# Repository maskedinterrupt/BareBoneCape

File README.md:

# BareBone Cape
### A BeagleBone Black Cape Template made in KiCad

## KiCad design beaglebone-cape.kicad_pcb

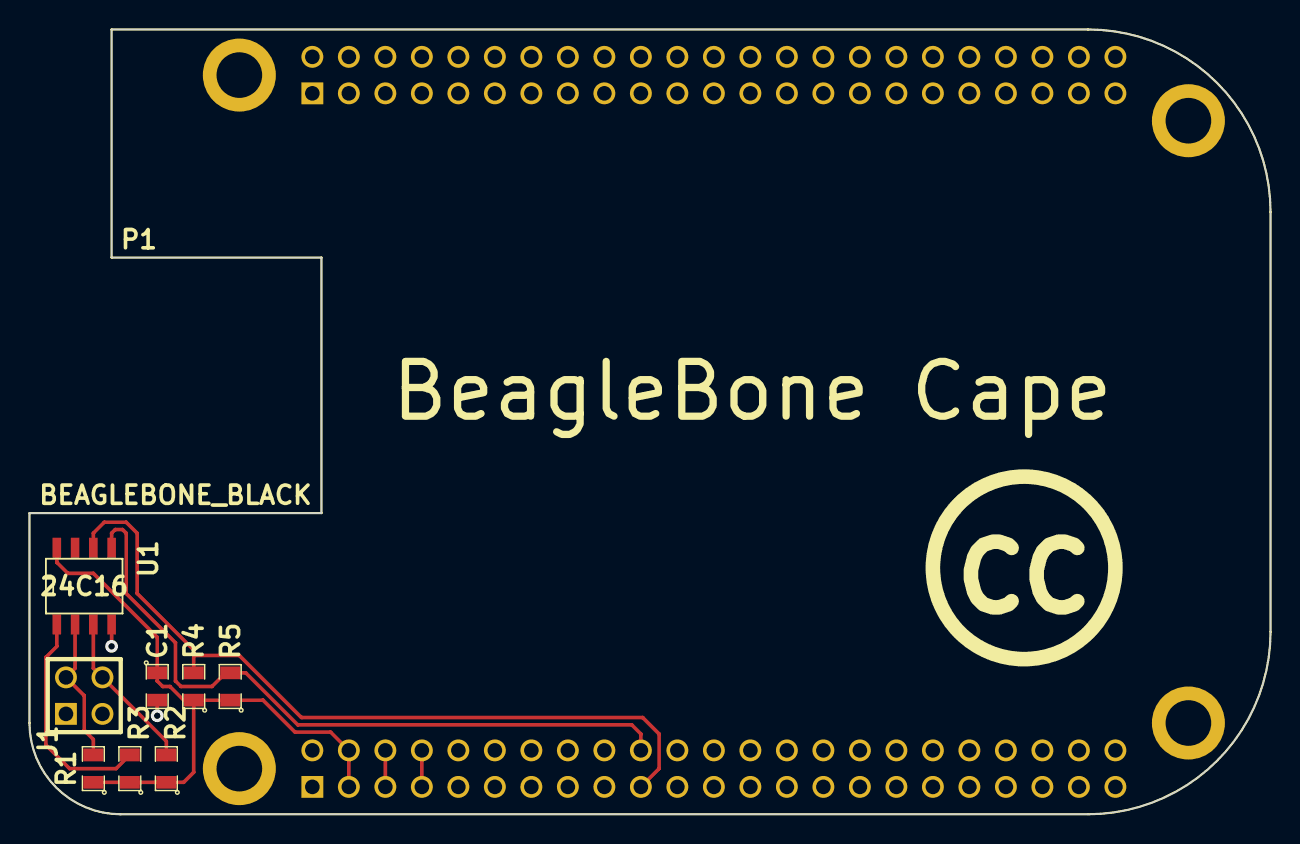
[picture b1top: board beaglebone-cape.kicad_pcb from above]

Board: 2 copper layers, 86.4 x 54.6 mm, 9 parts (0 on the bottom side), 9 nets.

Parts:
C1: 0.1u; SM0805
J1: CONN_2X2; PIN_ARRAY_2X2
P1: BEAGLEBONE_BLACK
R1, R2, R3: 4.7k; SM0805
R4, R5: 1.5k; SM0805
U1: 24C16; SO8E

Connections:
/A0: R3.2, U1.1
/A1: J1.2, R1.2, U1.2
/A2: J1.4, R2.2, U1.3
/DC_3.3V: C1.1, P1.B3, P1.B4, R1.1, R2.1, R3.1, R4.1, R5.1, U1.8
/I2C2_SCL: P1.B19, R4.2, U1.6
/I2C2_SDA: P1.B20, R5.2, U1.5
/SYS_5V: P1.B7, P1.B8
/VDD_5V: P1.B5, P1.B6
GND: C1.2, J1.1, J1.3, P1.A1, P1.A2, P1.B1, P1.B2, P1.B43, P1.B44, P1.B45, P1.B46, U1.4

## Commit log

2014-04-18 create beaglebone cape
2014-04-18 add readme
